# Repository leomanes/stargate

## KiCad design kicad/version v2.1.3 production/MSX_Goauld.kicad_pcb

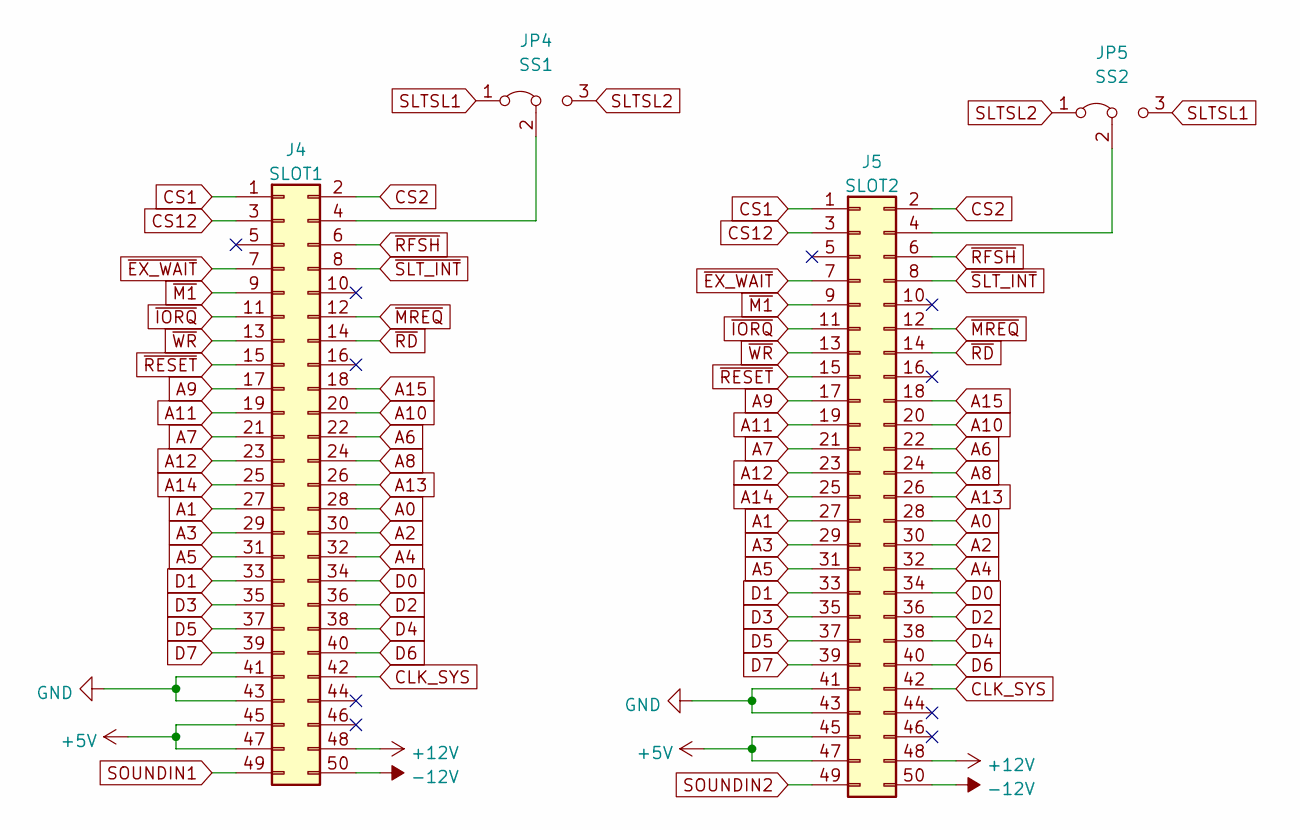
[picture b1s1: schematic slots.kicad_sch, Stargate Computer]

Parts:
J4: SLOT1; Conn_Edge_50P
J5: SLOT2; Conn_Edge_50P
JP4: SS1; SolderJumper-3_P1.3mm_Bridged12_Pad1.0x1.5mm_NumberLabels
JP5: SS2; SolderJumper-3_P1.3mm_Bridged12_Pad1.0x1.5mm_NumberLabels

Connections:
+5V: J4.45, J4.47, J5.45, J5.47; also elsewhere on the board
+12V: J4.48, J5.48; also elsewhere on the board
-12V: J4.50, J5.50; also elsewhere on the board
A0: J4.28, J5.28; also elsewhere on the board
A1: J4.27, J5.27; also elsewhere on the board
A2: J4.30, J5.30; also elsewhere on the board
A3: J4.29, J5.29; also elsewhere on the board
A4: J4.32, J5.32; also elsewhere on the board
A5: J4.31, J5.31; also elsewhere on the board
A6: J4.22, J5.22; also elsewhere on the board
A7: J4.21, J5.21; also elsewhere on the board
A8: J4.24, J5.24; also elsewhere on the board
A9: J4.17, J5.17; also elsewhere on the board
A10: J4.20, J5.20; also elsewhere on the board
A11: J4.19, J5.19; also elsewhere on the board
A12: J4.23, J5.23; also elsewhere on the board
A13: J4.26, J5.26; also elsewhere on the board
A14: J4.25, J5.25; also elsewhere on the board
A15: J4.18, J5.18; also elsewhere on the board
CLK_SYS: J4.42, J5.42; also elsewhere on the board
CS1: J4.1, J5.1; also elsewhere on the board
CS2: J4.2, J5.2; also elsewhere on the board
CS12: J4.3, J5.3; also elsewhere on the board
D0: J4.34, J5.34; also elsewhere on the board
D1: J4.33, J5.33; also elsewhere on the board
D2: J4.36, J5.36; also elsewhere on the board
D3: J4.35, J5.35; also elsewhere on the board
D4: J4.38, J5.38; also elsewhere on the board
D5: J4.37, J5.37; also elsewhere on the board
D6: J4.40, J5.40; also elsewhere on the board
D7: J4.39, J5.39; also elsewhere on the board
GND: J4.41, J4.43, J5.41, J5.43; also elsewhere on the board
INT: J4.8, J5.8; also elsewhere on the board
unnamed: J4.4, JP4.2 (C)
unnamed: J5.4, JP5.2 (C)
SLTSL1: JP4.1 (A), JP5.3 (B); also elsewhere on the board
SLTSL2: JP4.3 (B), JP5.1 (A); also elsewhere on the board
SOUNDIN1: J4.49; also elsewhere on the board
SOUNDIN2: J5.49; also elsewhere on the board
~EX_WAIT: J4.7, J5.7; also elsewhere on the board
~IORQ: J4.11, J5.11; also elsewhere on the board
~M1: J4.9, J5.9; also elsewhere on the board
~MREQ: J4.12, J5.12; also elsewhere on the board
~RD: J4.14, J5.14; also elsewhere on the board
~RESET: J4.15, J5.15; also elsewhere on the board
~RFSH: J4.6, J5.6; also elsewhere on the board
~WR: J4.13, J5.13; also elsewhere on the board

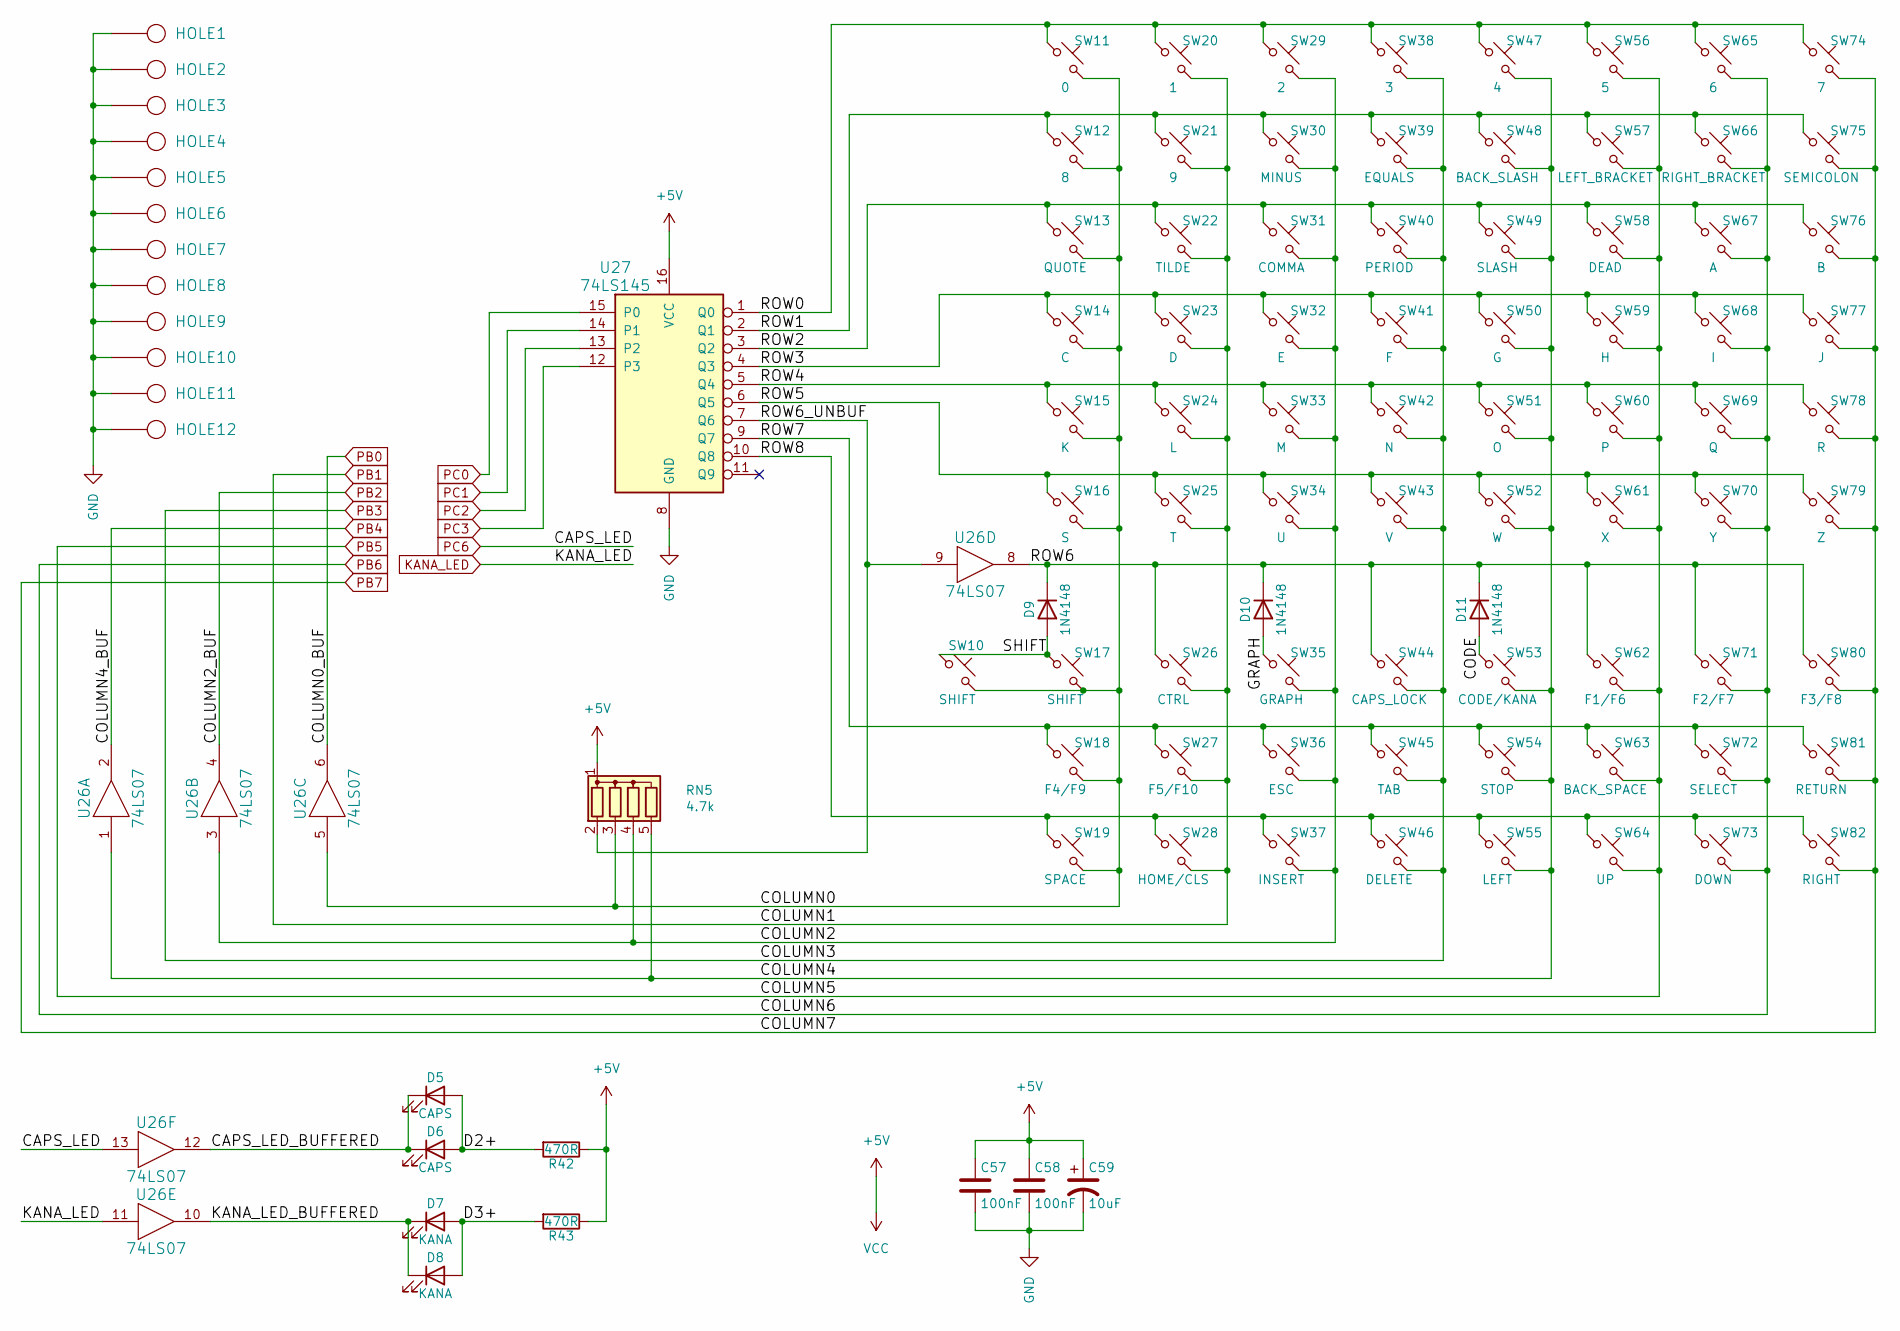
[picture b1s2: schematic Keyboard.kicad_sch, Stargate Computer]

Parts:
C57, C58: 100nF; CP_P5.00mm
C59: 10uF; CP_Radial_D5.0mm_P2.50mm
D5, D6: CAPS; LED_D3.0mm
D7, D8: KANA; LED_D3.0mm
D9, D10, D11: 1N4148; D_DO-35_SOD27_P7.62mm_Horizontal
HOLE1, HOLE2, HOLE3, HOLE4, HOLE5, HOLE6, HOLE7, HOLE8, HOLE9, HOLE12: HOLE; MountingHole_3mm_Pad_TopBottom_new
HOLE10, HOLE11: HOLE; MountingHole_2mm_Pad_TopBottom_new
R42, R43: 470R; R_Axial_DIN0204_L3.6mm_D1.6mm_P7.62mm_Horizontal
RN5: 4.7k; R_Array_SIP5
SW10: SHIFT; CHERRY_PCB_275H
SW11: 0; CHERRY_PCB_100H
SW12: 8; CHERRY_PCB_100H
SW13: QUOTE; CHERRY_PCB_100H
SW14: C; CHERRY_PCB_100H
SW15: K; CHERRY_PCB_100H
SW16: S; CHERRY_PCB_100H
SW17: SHIFT; CHERRY_PCB_225H
SW18: F4/F9; CHERRY_PCB_100H
SW19: SPACE; CHERRY_PCB_625H
SW20: 1; CHERRY_PCB_100H
SW21: 9; CHERRY_PCB_100H
SW22: TILDE; CHERRY_PCB_100H
SW23: D; CHERRY_PCB_100H
SW24: L; CHERRY_PCB_100H
SW25: T; CHERRY_PCB_100H
SW26: CTRL; CHERRY_PCB_125H
SW27: F5/F10; CHERRY_PCB_100H
SW28: HOME/CLS; CHERRY_PCB_100H
SW29: 2; CHERRY_PCB_100H
SW30: MINUS; CHERRY_PCB_100H
SW31: COMMA; CHERRY_PCB_100H
SW32: E; CHERRY_PCB_100H
SW33: M; CHERRY_PCB_100H
SW34: U; CHERRY_PCB_100H
SW35: GRAPH; CHERRY_PCB_125H
SW36: ESC; CHERRY_PCB_100H
SW37: INSERT; CHERRY_PCB_100H
SW38: 3; CHERRY_PCB_100H
SW39: EQUALS; CHERRY_PCB_100H
SW40: PERIOD; CHERRY_PCB_100H
SW41: F; CHERRY_PCB_100H
SW42: N; CHERRY_PCB_100H
SW43: V; CHERRY_PCB_100H
SW44: CAPS_LOCK; CHERRY_PCB_175H
SW45: TAB; CHERRY_PCB_150H
SW46: DELETE; CHERRY_PCB_100H
SW47: 4; CHERRY_PCB_100H
SW48: BACK_SLASH; CHERRY_PCB_150H
SW49: SLASH; CHERRY_PCB_100H
SW50: G; CHERRY_PCB_100H
SW51: O; CHERRY_PCB_100H
SW52: W; CHERRY_PCB_100H
SW53: CODE/KANA; CHERRY_PCB_125H
SW54: STOP; CHERRY_PCB_100H
SW55: LEFT; CHERRY_PCB_100H
SW56: 5; CHERRY_PCB_100H
SW57: LEFT_BRACKET; CHERRY_PCB_100H
SW58: DEAD; CHERRY_PCB_125H
SW59: H; CHERRY_PCB_100H
SW60: P; CHERRY_PCB_100H
SW61: X; CHERRY_PCB_100H
SW62: F1/F6; CHERRY_PCB_100H
SW63: BACK_SPACE; CHERRY_PCB_200H
SW64: UP; CHERRY_PCB_100H
SW65: 6; CHERRY_PCB_100H
SW66: RIGHT_BRACKET; CHERRY_PCB_100H
SW67: A; CHERRY_PCB_100H
SW68: I; CHERRY_PCB_100H
SW69: Q; CHERRY_PCB_100H
SW70: Y; CHERRY_PCB_100H
SW71: F2/F7; CHERRY_PCB_100H
SW72: SELECT; CHERRY_PCB_125H
SW73: DOWN; CHERRY_PCB_100H
SW74: 7; CHERRY_PCB_100H
SW75: SEMICOLON; CHERRY_PCB_100H
SW76: B; CHERRY_PCB_100H
SW77: J; CHERRY_PCB_100H
SW78: R; CHERRY_PCB_100H
SW79: Z; CHERRY_PCB_100H
SW80: F3/F8; CHERRY_PCB_100H
SW81: RETURN; CHERRY_PCB_225H
SW82: RIGHT; CHERRY_PCB_100H
U26: 74LS07; DIP-14_W7.62mm
U27: 74LS145; DIP-16_W7.62mm

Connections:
+5V: C57.1, C58.1, C59.1, R42.1, R43.1, RN5.1 (common), U26.14 (VCC), U27.16 (VCC); also elsewhere on the board
/Keyboard/CAPS_LED_BUFFERED: D5.1 (K), D6.1 (K), U26.12
/Keyboard/CODE: D11.2 (A), SW53.1
/Keyboard/COLUMN0: RN5.3 (R2), SW10.2, SW11.2, SW12.2, SW13.2, SW14.2, SW15.2, SW16.2, SW17.2, SW18.2, SW19.2, U26.5
/Keyboard/COLUMN2: RN5.4 (R3), SW29.2, SW30.2, SW31.2, SW32.2, SW33.2, SW34.2, SW35.2, SW36.2, SW37.2, U26.3
/Keyboard/COLUMN4: RN5.5 (R4), SW47.2, SW48.2, SW49.2, SW50.2, SW51.2, SW52.2, SW53.2, SW54.2, SW55.2, U26.1
/Keyboard/D2+: D5.2 (A), D6.2 (A), R42.2
/Keyboard/D3+: D7.2 (A), D8.2 (A), R43.2
/Keyboard/GRAPH: D10.2 (A), SW35.1
/Keyboard/KANA_LED_BUFFERED: D7.1 (K), D8.1 (K), U26.10
/Keyboard/ROW0: SW11.1, SW20.1, SW29.1, SW38.1, SW47.1, SW56.1, SW65.1, SW74.1, U27.1 (Q0)
/Keyboard/ROW1: SW12.1, SW21.1, SW30.1, SW39.1, SW48.1, SW57.1, SW66.1, SW75.1, U27.2 (Q1)
/Keyboard/ROW2: SW13.1, SW22.1, SW31.1, SW40.1, SW49.1, SW58.1, SW67.1, SW76.1, U27.3 (Q2)
/Keyboard/ROW3: SW14.1, SW23.1, SW32.1, SW41.1, SW50.1, SW59.1, SW68.1, SW77.1, U27.4 (Q3)
/Keyboard/ROW4: SW15.1, SW24.1, SW33.1, SW42.1, SW51.1, SW60.1, SW69.1, SW78.1, U27.5 (Q4)
/Keyboard/ROW5: SW16.1, SW25.1, SW34.1, SW43.1, SW52.1, SW61.1, SW70.1, SW79.1, U27.6 (Q5)
/Keyboard/ROW6: D9.1 (K), D10.1 (K), D11.1 (K), SW26.1, SW44.1, SW62.1, SW71.1, SW80.1, U26.8
/Keyboard/ROW6_UNBUF: RN5.2 (R1), U26.9, U27.7 (Q6)
/Keyboard/ROW7: SW18.1, SW27.1, SW36.1, SW45.1, SW54.1, SW63.1, SW72.1, SW81.1, U27.9 (Q7)
/Keyboard/ROW8: SW19.1, SW28.1, SW37.1, SW46.1, SW55.1, SW64.1, SW73.1, SW82.1, U27.10 (Q8)
/Keyboard/SHIFT: D9.2 (A), SW10.1, SW17.1
GND: C57.2, C58.2, C59.2, HOLE1.1, HOLE2.1, HOLE3.1, HOLE4.1, HOLE5.1, HOLE6.1, HOLE7.1, HOLE8.1, HOLE9.1, HOLE10.1, HOLE11.1, HOLE12.1, U26.7 (GND), U27.8 (GND); also elsewhere on the board
KANA_LED: U26.11; also elsewhere on the board
PB0: U26.6; also elsewhere on the board
PB1: SW20.2, SW21.2, SW22.2, SW23.2, SW24.2, SW25.2, SW26.2, SW27.2, SW28.2; also elsewhere on the board
PB2: U26.4; also elsewhere on the board
PB3: SW38.2, SW39.2, SW40.2, SW41.2, SW42.2, SW43.2, SW44.2, SW45.2, SW46.2; also elsewhere on the board
PB4: U26.2; also elsewhere on the board
PB5: SW56.2, SW57.2, SW58.2, SW59.2, SW60.2, SW61.2, SW62.2, SW63.2, SW64.2; also elsewhere on the board
PB6: SW65.2, SW66.2, SW67.2, SW68.2, SW69.2, SW70.2, SW71.2, SW72.2, SW73.2; also elsewhere on the board
PB7: SW74.2, SW75.2, SW76.2, SW77.2, SW78.2, SW79.2, SW80.2, SW81.2, SW82.2; also elsewhere on the board
PC0: U27.15 (P0); also elsewhere on the board
PC1: U27.14 (P1); also elsewhere on the board
PC2: U27.13 (P2); also elsewhere on the board
PC3: U27.12 (P3); also elsewhere on the board
PC6: U26.13; also elsewhere on the board

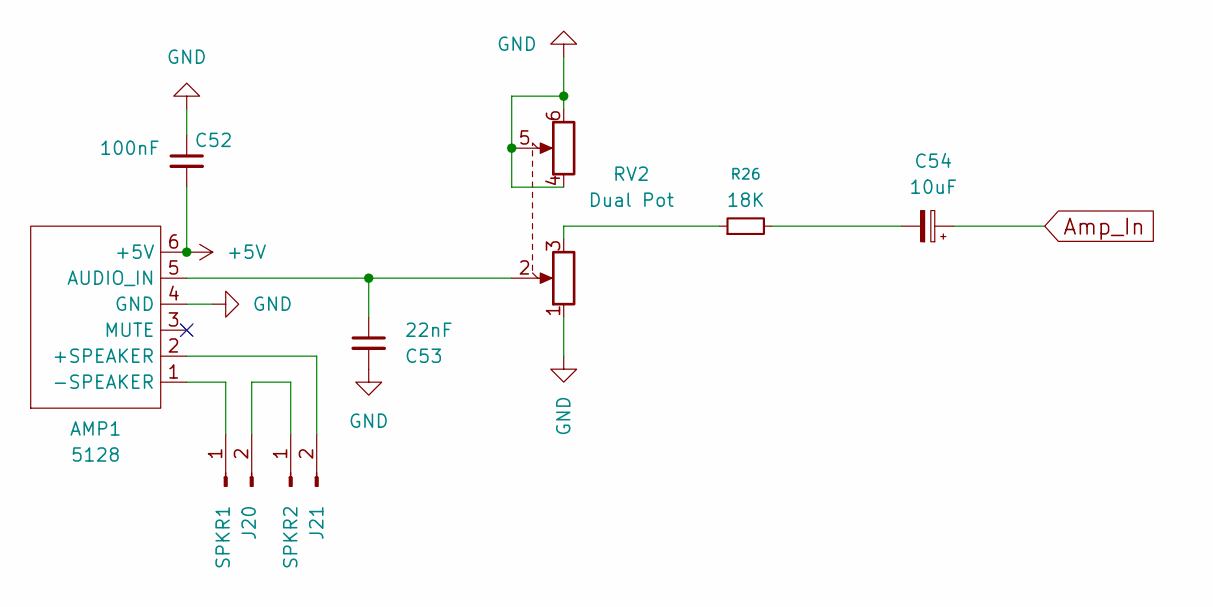
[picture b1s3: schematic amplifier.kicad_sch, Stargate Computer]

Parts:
AMP1: 5128; Amp5128
C52: 100nF; CP_P5.00mm
C53: 22nF; CP_P5.00mm
C54: 10uF; CP_Radial_D5.0mm_P2.50mm
J20: SPKR1; PinHeader_1x02_P2.54mm_Vertical
J21: SPKR2; PinHeader_1x02_P2.54mm_Vertical
R26: 18K; R_Axial_DIN0204_L3.6mm_D1.6mm_P7.62mm_Horizontal
RV2: Dual Pot; Potentiometer_Alps_RK097_Dual_Horizontal

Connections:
+5V: AMP1.6 (+5V), C52.2; also elsewhere on the board
Amp_In: C54.1; also elsewhere on the board
GND: AMP1.4 (GND), C52.1, C53.2, RV2.1, RV2.4, RV2.5, RV2.6; also elsewhere on the board
unnamed: AMP1.2 (+SPEAKER), J21.2
unnamed: AMP1.1 (-SPEAKER), J20.1
unnamed: AMP1.5 (AUDIO_IN), C53.1, RV2.2
unnamed: C54.2, R26.2
unnamed: J20.2, J21.1
unnamed: R26.1, RV2.3

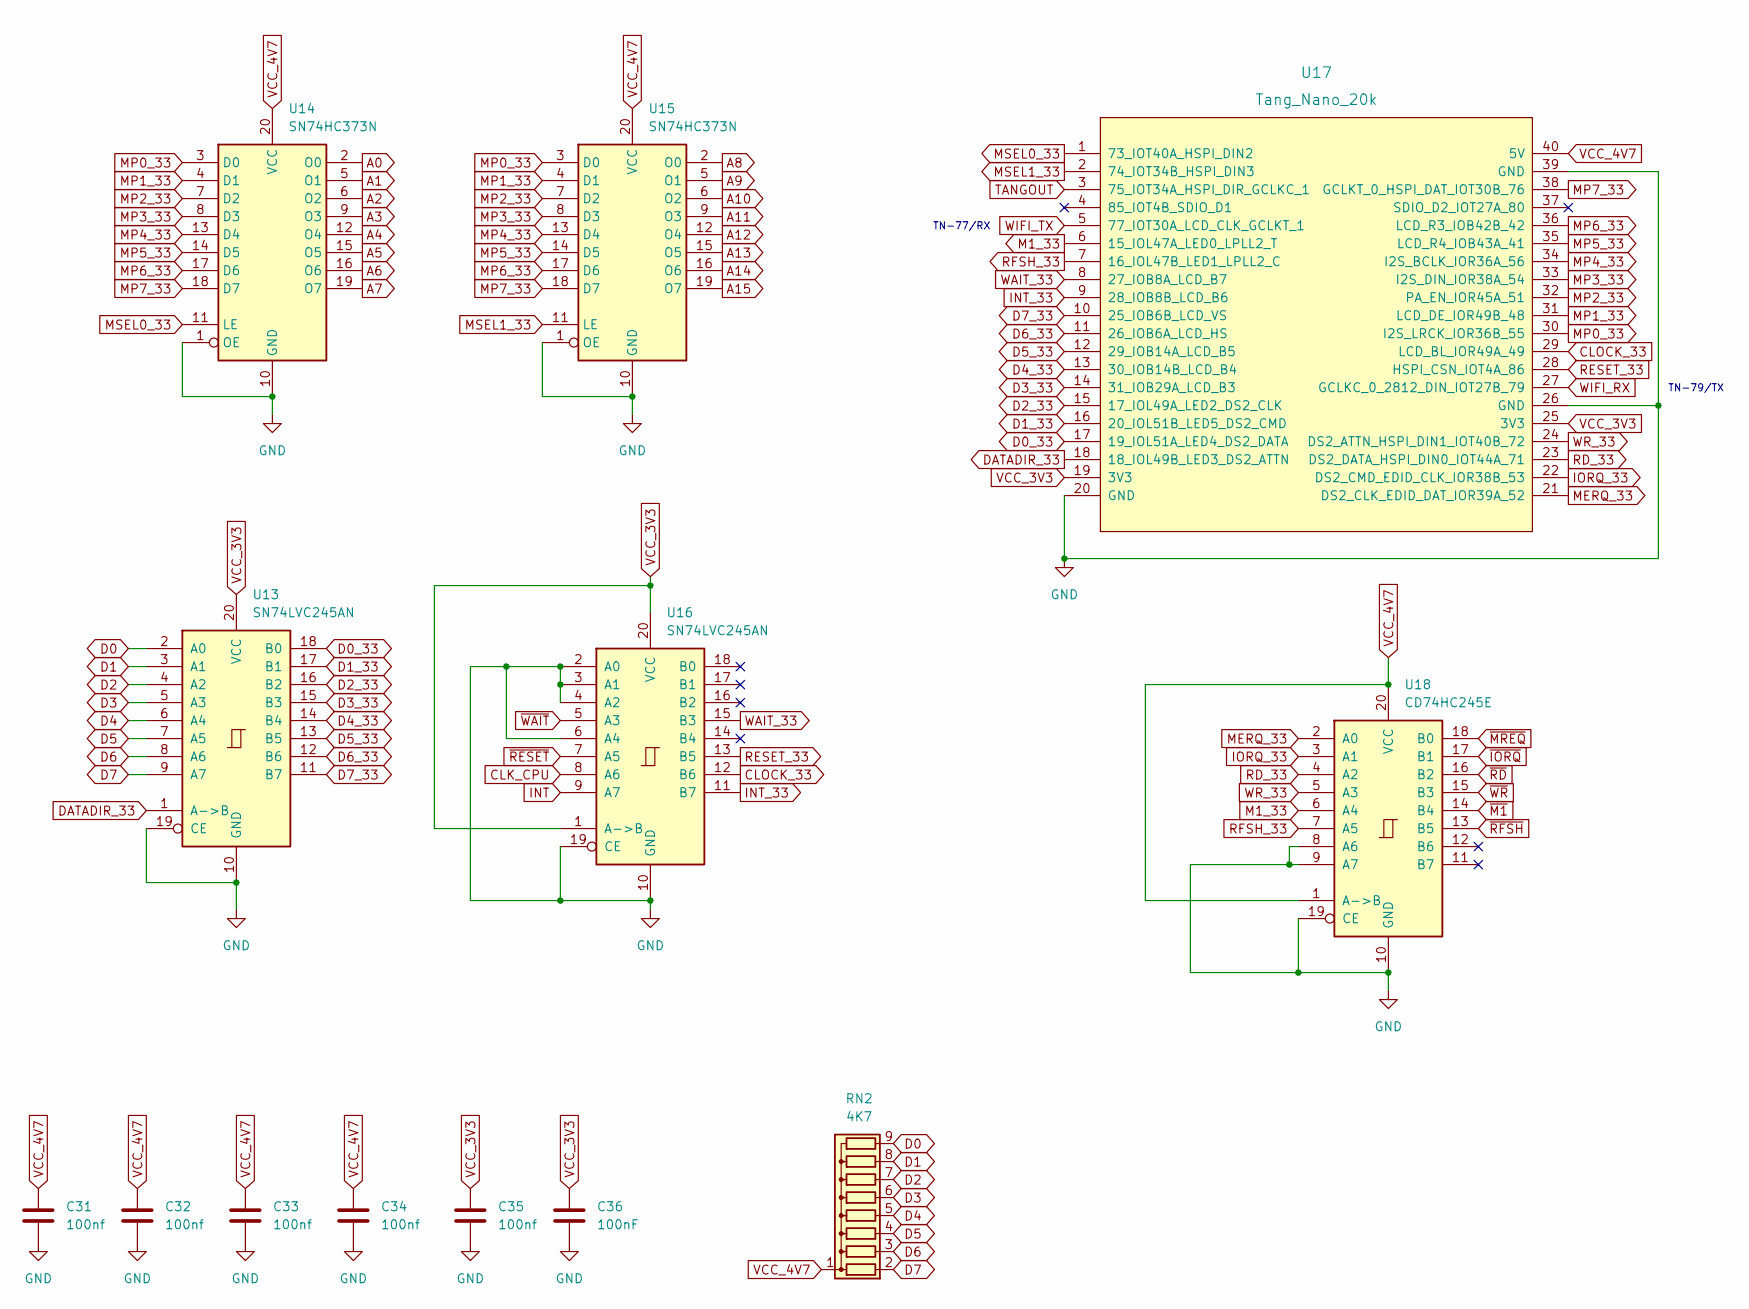
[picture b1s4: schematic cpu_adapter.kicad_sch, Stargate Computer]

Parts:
C31, C32, C33, C34, C35: 100nf; CP_P5.00mm
C36: 100nF; CP_P5.00mm
RN2: 4K7; R_Array_SIP9
U13, U16: SN74LVC245AN; DIP-20_W7.62mm_LongPads
U14, U15: SN74HC373N; DIP-20_W7.62mm_LongPads
U17: Tang_Nano_20k
U18: CD74HC245E; DIP-20_W7.62mm_LongPads

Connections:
A0: U14.2 (O0); also elsewhere on the board
A1: U14.5 (O1); also elsewhere on the board
A2: U14.6 (O2); also elsewhere on the board
A3: U14.9 (O3); also elsewhere on the board
A4: U14.12 (O4); also elsewhere on the board
A5: U14.15 (O5); also elsewhere on the board
A6: U14.16 (O6); also elsewhere on the board
A7: U14.19 (O7); also elsewhere on the board
A8: U15.2 (O0); also elsewhere on the board
A9: U15.5 (O1); also elsewhere on the board
A10: U15.6 (O2); also elsewhere on the board
A11: U15.9 (O3); also elsewhere on the board
A12: U15.12 (O4); also elsewhere on the board
A13: U15.15 (O5); also elsewhere on the board
A14: U15.16 (O6); also elsewhere on the board
A15: U15.19 (O7); also elsewhere on the board
CLK_CPU: U16.8 (A6); also elsewhere on the board
CLOCK_33: U16.12 (B6), U17.29 (LCD_BL_IOR49A_49)
D0: RN2.9 (R8), U13.2 (A0); also elsewhere on the board
D0_33: U13.18 (B0), U17.17 (19_IOL51A_LED4_DS2_DATA)
D1: RN2.8 (R7), U13.3 (A1); also elsewhere on the board
D1_33: U13.17 (B1), U17.16 (20_IOL51B_LED5_DS2_CMD)
D2: RN2.7 (R6), U13.4 (A2); also elsewhere on the board
D2_33: U13.16 (B2), U17.15 (17_IOL49A_LED2_DS2_CLK)
D3: RN2.6 (R5), U13.5 (A3); also elsewhere on the board
D3_33: U13.15 (B3), U17.14 (31_IOB29A_LCD_B3)
D4: RN2.5 (R4), U13.6 (A4); also elsewhere on the board
D4_33: U13.14 (B4), U17.13 (30_IOB14B_LCD_B4)
D5: RN2.4 (R3), U13.7 (A5); also elsewhere on the board
D5_33: U13.13 (B5), U17.12 (29_IOB14A_LCD_B5)
D6: RN2.3 (R2), U13.8 (A6); also elsewhere on the board
D6_33: U13.12 (B6), U17.11 (26_IOB6A_LCD_HS)
D7: RN2.2 (R1), U13.9 (A7); also elsewhere on the board
D7_33: U13.11 (B7), U17.10 (25_IOB6B_LCD_VS)
DATADIR_33: U13.1 (A->B), U17.18 (18_IOL49B_LED3_DS2_ATTN)
GND: C31.2, C32.2, C33.2, C34.2, C35.2, C36.2, U13.10 (GND), U13.19 (CE), U14.1 (OE), U14.10 (GND), U15.1 (OE), U15.10 (GND), U16.2 (A0), U16.3 (A1), U16.4 (A2), U16.6 (A4), U16.10 (GND), U16.19 (CE), U17.20 (GND), U17.26 (GND), U17.39 (GND), U18.8 (A6), U18.9 (A7), U18.10 (GND), U18.19 (CE); also elsewhere on the board
INT: U16.9 (A7); also elsewhere on the board
INT_33: U16.11 (B7), U17.9 (28_IOB8B_LCD_B6)
IORQ_33: U17.22 (DS2_CMD_EDID_CLK_IOR38B_53), U18.3 (A1)
M1_33: U17.6 (15_IOL47A_LED0_LPLL2_T), U18.6 (A4)
MERQ_33: U17.21 (DS2_CLK_EDID_DAT_IOR39A_52), U18.2 (A0)
MP0_33: U14.3 (D0), U15.3 (D0), U17.30 (I2S_LRCK_IOR36B_55)
MP1_33: U14.4 (D1), U15.4 (D1), U17.31 (LCD_DE_IOR49B_48)
MP2_33: U14.7 (D2), U15.7 (D2), U17.32 (PA_EN_IOR45A_51)
MP3_33: U14.8 (D3), U15.8 (D3), U17.33 (I2S_DIN_IOR38A_54)
MP4_33: U14.13 (D4), U15.13 (D4), U17.34 (I2S_BCLK_IOR36A_56)
MP5_33: U14.14 (D5), U15.14 (D5), U17.35 (LCD_R4_IOB43A_41)
MP6_33: U14.17 (D6), U15.17 (D6), U17.36 (LCD_R3_IOB42B_42)
MP7_33: U14.18 (D7), U15.18 (D7), U17.38 (GCLKT_0_HSPI_DAT_IOT30B_76)
MSEL0_33: U14.11 (LE), U17.1 (73_IOT40A_HSPI_DIN2)
MSEL1_33: U15.11 (LE), U17.2 (74_IOT34B_HSPI_DIN3)
RD_33: U17.23 (DS2_DATA_HSPI_DIN0_IOT44A_71), U18.4 (A2)
RESET_33: U16.13 (B5), U17.28 (HSPI_CSN_IOT4A_86)
RFSH_33: U17.7 (16_IOL47B_LED1_LPLL2_C), U18.7 (A5)
TANGOUT: U17.3 (75_IOT34A_HSPI_DIR_GCLKC_1); also elsewhere on the board
VCC_3V3: C35.1, C36.1, U13.20 (VCC), U16.1 (A->B), U16.20 (VCC), U17.19 (3V3), U17.25 (3V3); also elsewhere on the board
VCC_4V7: C31.1, C32.1, C33.1, C34.1, RN2.1 (common), U14.20 (VCC), U15.20 (VCC), U17.40 (5V), U18.1 (A->B), U18.20 (VCC); also elsewhere on the board
WAIT_33: U16.15 (B3), U17.8 (27_IOB8A_LCD_B7)
WIFI_RX: U17.27 (GCLKC_0_2812_DIN_IOT27B_79); also elsewhere on the board
WIFI_TX: U17.5 (77_IOT30A_LCD_CLK_GCLKT_1); also elsewhere on the board
WR_33: U17.24 (DS2_ATTN_HSPI_DIN1_IOT40B_72), U18.5 (A3)
~IORQ: U18.17 (B1); also elsewhere on the board
~M1: U18.14 (B4); also elsewhere on the board
~MREQ: U18.18 (B0); also elsewhere on the board
~RD: U18.16 (B2); also elsewhere on the board
~RESET: U16.7 (A5); also elsewhere on the board
~RFSH: U18.13 (B5); also elsewhere on the board
~WAIT: U16.5 (A3); also elsewhere on the board
~WR: U18.15 (B3); also elsewhere on the board

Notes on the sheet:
TN-77/RX
TN-79/TX

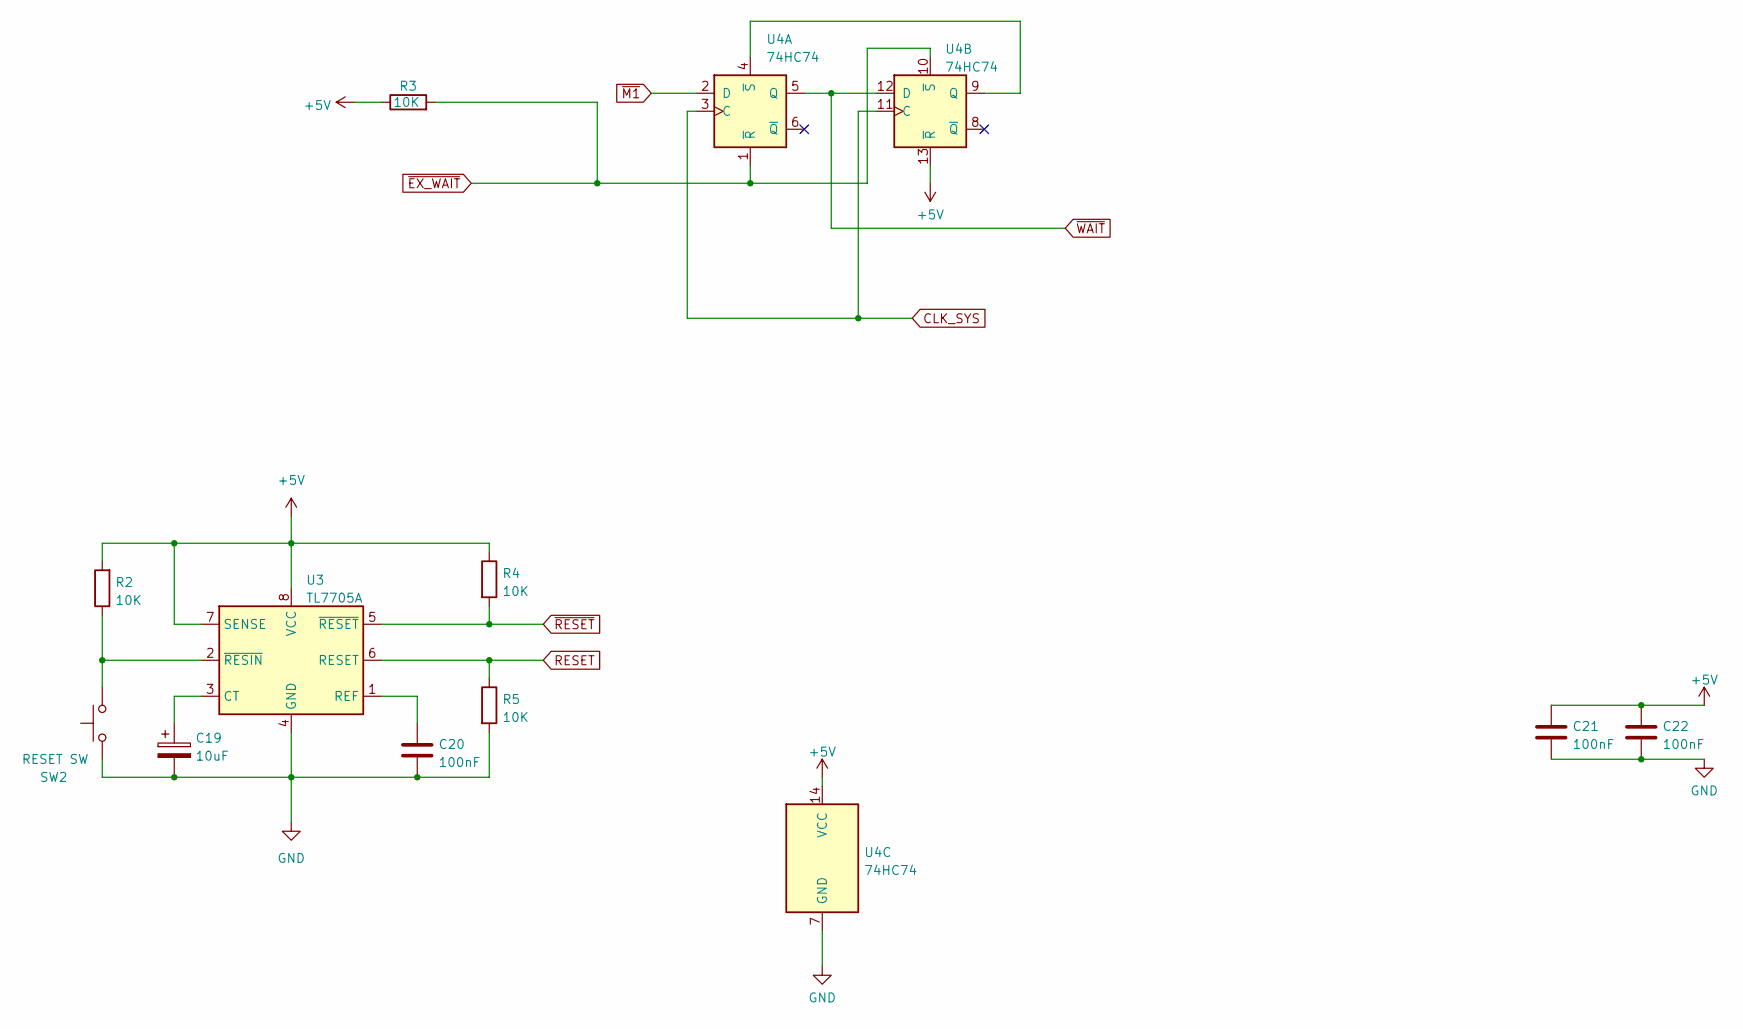
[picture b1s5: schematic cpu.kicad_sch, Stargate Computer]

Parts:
C19: 10uF; CP_Radial_D5.0mm_P2.50mm
C20, C21, C22: 100nF; CP_P5.00mm
R2, R3, R4, R5: 10K; R_Axial_DIN0204_L3.6mm_D1.6mm_P7.62mm_Horizontal
SW2: RESET SW; SW_Tactile_SPST_Angled_PTS645Vx83-2LFS
U3: TL7705A; DIP-8_W7.62mm_LongPads
U4: 74HC74; DIP-14_W7.62mm_LongPads

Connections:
+5V: C21.1, C22.1, R2.2, R3.1, R4.1, U3.7 (SENSE), U3.8 (VCC), U4.13 (~R), U4.14 (VCC); also elsewhere on the board
CLK_SYS: U4.3 (C), U4.11 (C); also elsewhere on the board
GND: C19.2, C20.2, C21.2, C22.2, R5.2, SW2.1, U3.4 (GND), U4.7 (GND); also elsewhere on the board
unnamed: C19.1, U3.3 (CT)
unnamed: C20.1, U3.1 (REF)
unnamed: R2.1, SW2.2, U3.2 (~RESIN)
unnamed: U4.4 (~S), U4.9 (Q)
RESET: R5.1, U3.6 (RESET); also elsewhere on the board
~EX_WAIT: R3.2, U4.1 (~R), U4.10 (~S); also elsewhere on the board
~M1: U4.2 (D); also elsewhere on the board
~RESET: R4.2, U3.5 (~RESET); also elsewhere on the board
~WAIT: U4.5 (Q), U4.12 (D); also elsewhere on the board

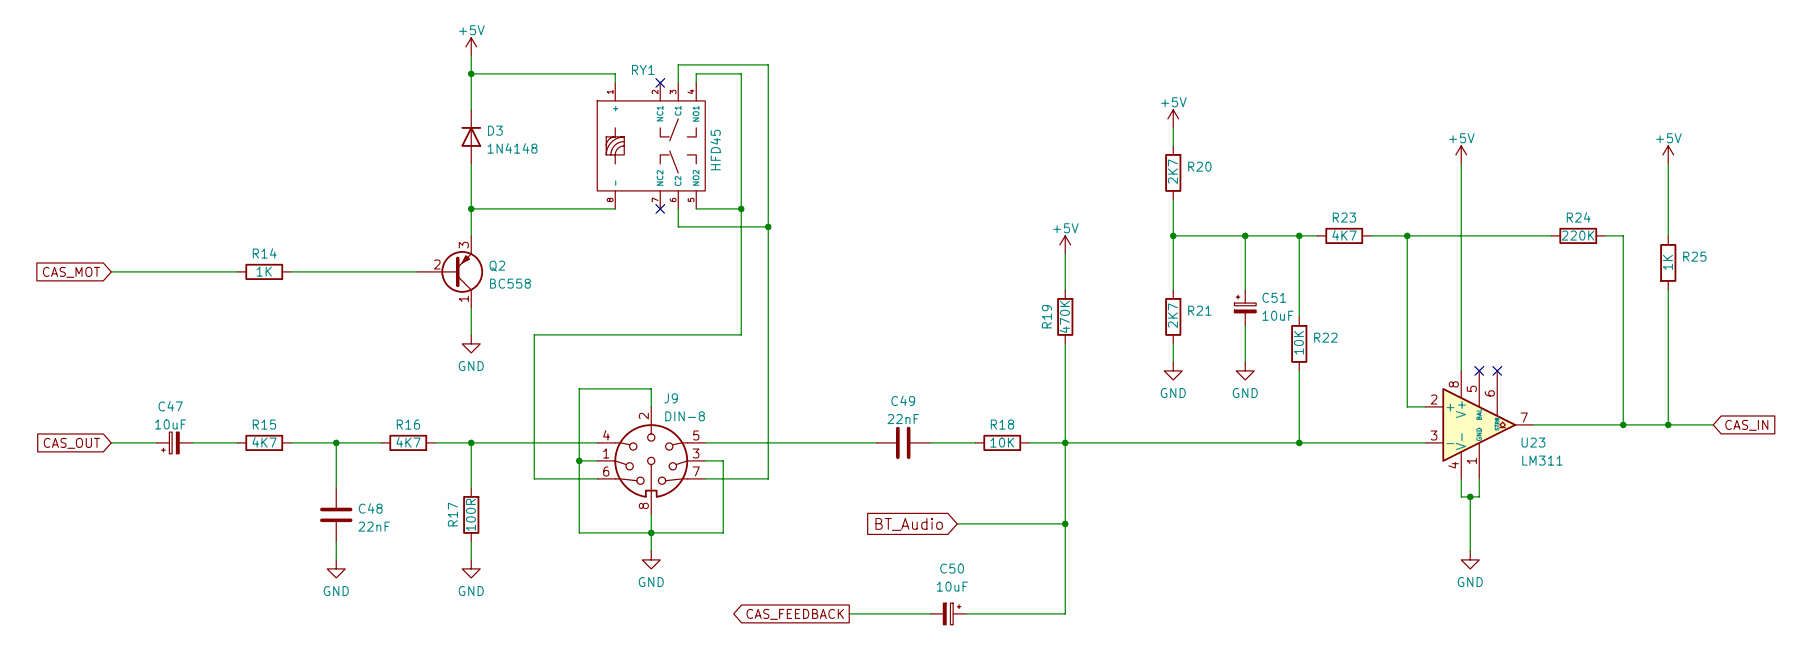
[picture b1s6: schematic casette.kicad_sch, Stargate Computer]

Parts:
C47, C50, C51: 10uF; CP_Radial_D5.0mm_P2.50mm
C48, C49: 22nF; C_Disc_D3.0mm_W2.0mm_P2.50mm
D3: 1N4148; D_DO-35_SOD27_P7.62mm_Horizontal
J9: DIN-8; DIN8
Q2: BC558; TO-92
R14, R25: 1K; R_Axial_DIN0204_L3.6mm_D1.6mm_P7.62mm_Horizontal
R15, R16, R23: 4K7; R_Axial_DIN0204_L3.6mm_D1.6mm_P7.62mm_Horizontal
R17: 100R; R_Axial_DIN0204_L3.6mm_D1.6mm_P7.62mm_Horizontal
R18, R22: 10K; R_Axial_DIN0204_L3.6mm_D1.6mm_P7.62mm_Horizontal
R19: 470K; R_Axial_DIN0204_L3.6mm_D1.6mm_P7.62mm_Horizontal
R20, R21: 2K7; R_Axial_DIN0204_L3.6mm_D1.6mm_P7.62mm_Horizontal
R24: 220K; R_Axial_DIN0204_L3.6mm_D1.6mm_P7.62mm_Horizontal
RY1: HFD45
U23: LM311; DIP-8_W7.62mm_LongPads

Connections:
+5V: D3.1 (K), R19.2, R20.2, R25.1, RY1.1 (+), U23.8 (V+); also elsewhere on the board
BT_Audio: C50.1, R18.2, R19.1, R22.1, U23.3 (-); also elsewhere on the board
CAS_FEEDBACK: C50.2; also elsewhere on the board
CAS_IN: R24.2, R25.2, U23.7; also elsewhere on the board
CAS_MOT: R14.1; also elsewhere on the board
CAS_OUT: C47.1; also elsewhere on the board
GND: C48.1, C51.2, J9.1, J9.2, J9.3, J9.8, Q2.1 (C), R17.1, R21.1, U23.1 (GND), U23.4 (V-); also elsewhere on the board
unnamed: C47.2, R15.1
unnamed: C48.2, R15.2, R16.1
unnamed: C49.1, J9.5
unnamed: C49.2, R18.1
unnamed: C51.1, R20.1, R21.2, R22.2, R23.1
unnamed: D3.2 (A), Q2.3 (E), RY1.8 (-)
unnamed: J9.4, R16.2, R17.2
unnamed: Q2.2 (B), R14.2
unnamed: J9.7, RY1.3 (C1), RY1.6 (C2)
unnamed: J9.6, RY1.4 (NO1), RY1.5 (NO2)
unnamed: R23.2, R24.1, U23.2 (+)
